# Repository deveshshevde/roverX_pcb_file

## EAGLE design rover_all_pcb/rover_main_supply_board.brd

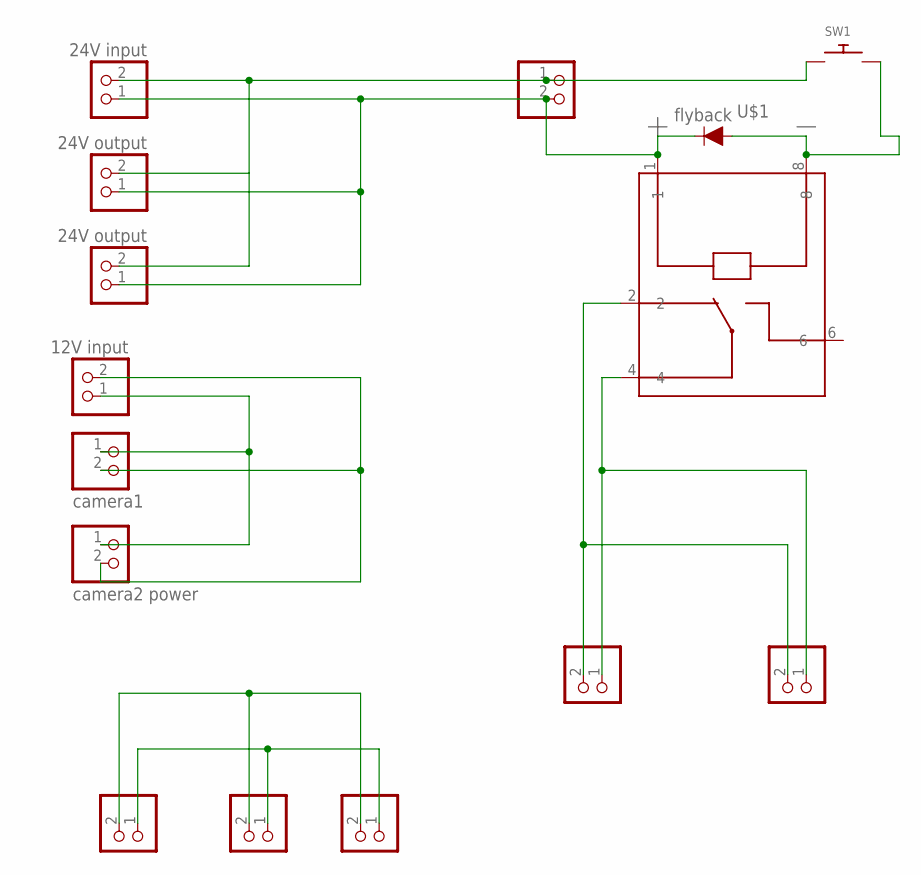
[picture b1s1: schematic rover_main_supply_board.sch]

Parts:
5VINPUT: 5V INPUT; 1X02
D1: flyback; DIODE-1N4148
JP1: 24V input; 1X02
JP2, JP3, JP4: PINHD-1X2; 1X02
JP5: camera1; 1X02
JP6, JP9, JP10: camera2 power; 1X02
JP7, JP11: 24V output; 1X02
JP8: 12V input; 1X02
SW1: SWITCH_PUSHBUTTONSOFTTOUCHSMD_SJ; PUSHBUTTON_SMD_SJ
U$1: ADJ1505005; DJ_1_FORM_C_SSS

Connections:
unnamed: JP1.2, JP2.1, JP7.2, SW1.P$1
unnamed: 5VINPUT.1, JP9.1, JP10.1
unnamed: D1.A, SW1.P$2, U$1.8
unnamed: JP3.2, JP4.2, U$1.2
unnamed: JP3.1, JP4.1, U$1.4
unnamed: JP5.2, JP6.2, JP8.2
unnamed: JP5.1, JP6.1, JP8.1
unnamed: D1.C, JP1.1, JP2.2, JP7.1, JP11.1, U$1.1
unnamed: 5VINPUT.2, JP9.2, JP10.2

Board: 2 copper layers, 15 parts (0 on the bottom side), 9 nets, no tracks yet.

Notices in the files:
parts and their libraries:
SparkFun-DiscreteSemi: Licensing: Creative Commons ShareAlike 4.0 International - https://creativecommons.org/licenses/by-sa/4.0
